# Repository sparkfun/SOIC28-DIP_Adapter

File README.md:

SOIC28 DIP Adapter
==================
[
*SparkFun SOIC28 to DIP Adapter (BOB-00496)*](https://www.sparkfun.com/products/496)

This pcb breaks out 28 pin SOIC packages to standard 0.1" headers. 

Repository Contents
-------------------

* **/Hardware** - All Eagle design files (.brd, .sch)

License Information
-------------------
The hardware is released under [Creative Commons ShareAlike 4.0 International](https://creativecommons.org/licenses/by-sa/4.0/).
The code is beerware; if you see me (or any other SparkFun employee) at the local, and you've found our code helpful, please buy us a round!

Distributed as-is; no warranty is given.

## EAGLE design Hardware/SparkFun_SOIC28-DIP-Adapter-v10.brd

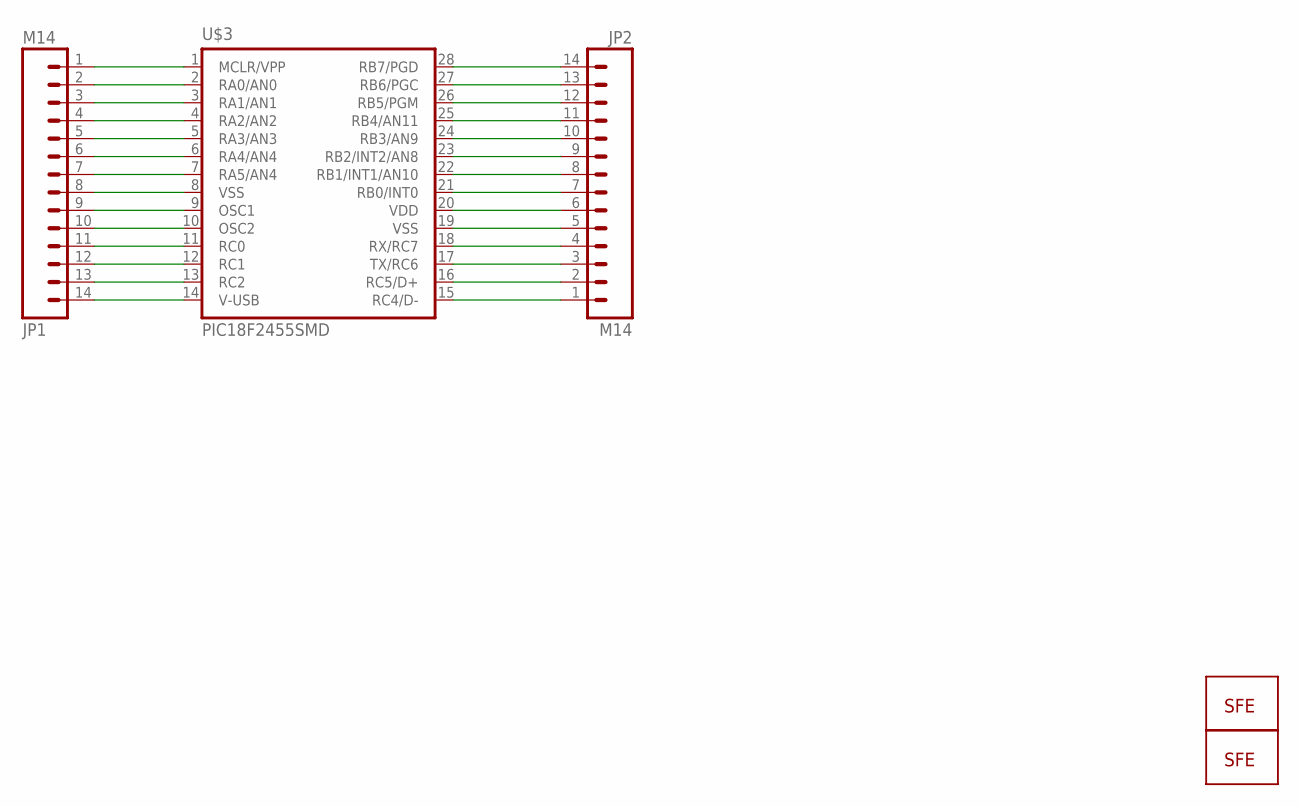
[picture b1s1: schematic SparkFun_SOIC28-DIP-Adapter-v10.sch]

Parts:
JP1, JP2: M14; 1X14
U$1: LOGO-SFESK; SFE-LOGO-FLAME
U$2: LOGO-SFENEW; SFE-NEW-WEBLOGO
U$3: PIC18F2455SMD; SO-28W

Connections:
unnamed: JP1.1, U$3.1 (MCLR/VPP)
unnamed: JP1.2, U$3.2 (RA0/AN0)
unnamed: JP1.3, U$3.3 (RA1/AN1)
unnamed: JP1.4, U$3.4 (RA2/AN2)
unnamed: JP1.5, U$3.5 (RA3/AN3)
unnamed: JP1.6, U$3.6 (RA4/AN4)
unnamed: JP1.7, U$3.7 (RA5/AN4)
unnamed: JP1.8, U$3.8 (VSS)
unnamed: JP1.9, U$3.9 (OSC1)
unnamed: JP1.10, U$3.10 (OSC2)
unnamed: JP1.11, U$3.11 (RC0)
unnamed: JP1.12, U$3.12 (RC1)
unnamed: JP1.13, U$3.13 (RC2)
unnamed: JP1.14, U$3.14 (V-USB)
unnamed: JP2.1, U$3.15 (RC4/D-)
unnamed: JP2.2, U$3.16 (RC5/D+)
unnamed: JP2.3, U$3.17 (TX/RC6)
unnamed: JP2.4, U$3.18 (RX/RC7)
unnamed: JP2.5, U$3.19 (VSS)
unnamed: JP2.6, U$3.20 (VDD)
unnamed: JP2.7, U$3.21 (RB0/INT0)
unnamed: JP2.8, U$3.22 (RB1/INT1/AN10)
unnamed: JP2.9, U$3.23 (RB2/INT2/AN8)
unnamed: JP2.10, U$3.24 (RB3/AN9)
unnamed: JP2.11, U$3.25 (RB4/AN11)
unnamed: JP2.12, U$3.26 (RB5/PGM)
unnamed: JP2.13, U$3.27 (RB6/PGC)
unnamed: JP2.14, U$3.28 (RB7/PGD)

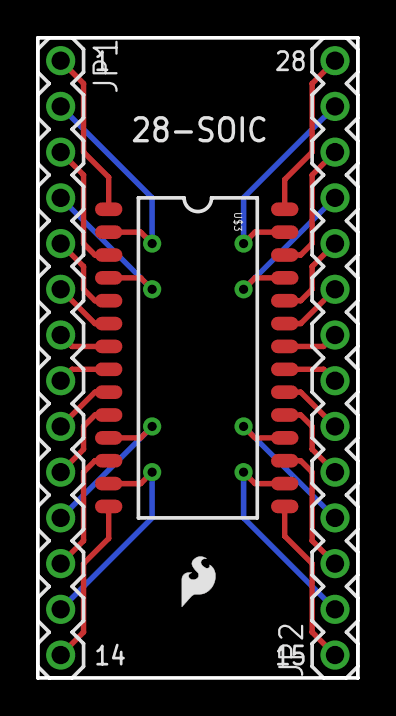
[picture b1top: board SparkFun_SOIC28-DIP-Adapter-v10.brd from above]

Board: 2 copper layers, 17.8 x 35.6 mm, 5 parts (1 on the bottom side), 28 nets.

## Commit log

2015-01-06 Initial file commit
